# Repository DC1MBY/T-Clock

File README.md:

# T-Clock: A Nixie tube clock build from transistors only

The first working transistor demo just had its 75th anniversary: https://en.wikipedia.org/wiki/History_of_the_transistor How to better celebrate it than having (103 times) fun with transistors? Some time back I discovered in the German magazine Funkschau 1969 #2, #3 and #10 the article "Digital-Uhr zum Selbstbau", a copy of it can be found here: http://www.nixieuhren.de/downloads/digitaluhrfunkschau.pdf 
It is a Nixie clock design completely based on transistors. I always wanted to build one of these. When I found out that Kicad supports auto routing (freeRouting/LayoutEditor), that became much more feasible. This repository contains the PCB designs as well as OpenScad designs for the case and the spacer for the Nixies.

**Warning: Nixie tubes require high voltages which can be lethal. Please be careful!**

## Changes compared to the original

### Prescaler

I'm living in US, so I had to modify the prescaler from 50Hz to 60Hz mains frequency. /60 can be very easy implemented as /10 followed by /6. This allowed to re-use the PCBs of the first and second digit, just the decoding/high voltage transistors aren't populated on these PCBs. Luckily the usual PCB prototype manufactures always send a couple of copies of each ordered PCB, very handy for that.

### Schmitt-Trigger

The Schmitt trigger for converting the sinusoidal mains signal to a square wave feeding the prescaler was converted from Ge to Si. Because the circuit is small, I didn't develop a pcb for it but implemented it on a piece of perfboard. 

### Power Supply

Power source is a 12VAC 1.5A wall wart, this way no routing of mains voltage is needed. The high voltage for the Nixie tubes is generated by a small reverse operated transformer. Because of the high DC resistance of the transformer the supply is very soft and reaching the correct voltage (about 170V) is a bit critical. Therefore the rectified 12V was added in order to reach the required voltage. If this is needed or not will depend on the type of transformer. The Ge transistors of the 12V regulator were replaced by Si ones. The pass transistor needs a heatsink. A perfboard was used for the power supply. 

## Obtaining the parts

All components are easily obtainable except for the Nixie tubes. The IN-12 Nixie tube can still be found on ebay. Because the decimal point isn't used, both the IN-12A and IN-12B version will work fine.

## Block Diagram

## Mechanical

### Boards

The boards are stacked with 25mm M3 spacers and 10mm M3 spacers. The stack will be mounted to the case.

### Nixie

Even more difficult to source than the Nixie tubes themselves are sockets for them. Therefore I soldered the Nixie tubes directly to the PCB. I've seen this method first in Russian test equipment offered on a flea market. For equally spacing the Nixie from the PCB a 3d printed spacer is used (in12b.scad).  

### Case

The case is based on the fantastic Ultimate Box Maker https://github.com/jbebel/Ultimate-Box-Maker. The pcb mounts and the tabs are using M2.5 metal threaded inserts https://www.amazon.com/gp/product/B07NBPGTY2 .

The letters in the back panel are painted black with a sharpie. 

The screws can be installed with an Allen key through the vent. For the picture I didn't have the front panel installed yet, but the front panel needs to be installed before the screws. In this version of the case the tab was 2 mm thick and I broke one off. Therefore I made it 4mm thick. It might be best to print it with 100% infill for added stability.

## Summary

Things I might change if I'd redesign it:
- Move the Nixies to the center of the pcb for better looks
- Add a second mounting hole to the pcbs on the lower side (I made the usual mistake to first layout the pcbs and then think about the case)
- Change to SMD components. I forgot how tedious it is to bend the leads and clip them.   

That was a fun project. It turned out to be quite easy to build a more than 50 years old design today. I fear one of today's "modern" Nixie clock designs based on an microcontroller will be much harder to build in 50 years from now, the toolchain for the controller will not work with Windows 2070, USB20 will be incompatible with USB2.0, ... ;)

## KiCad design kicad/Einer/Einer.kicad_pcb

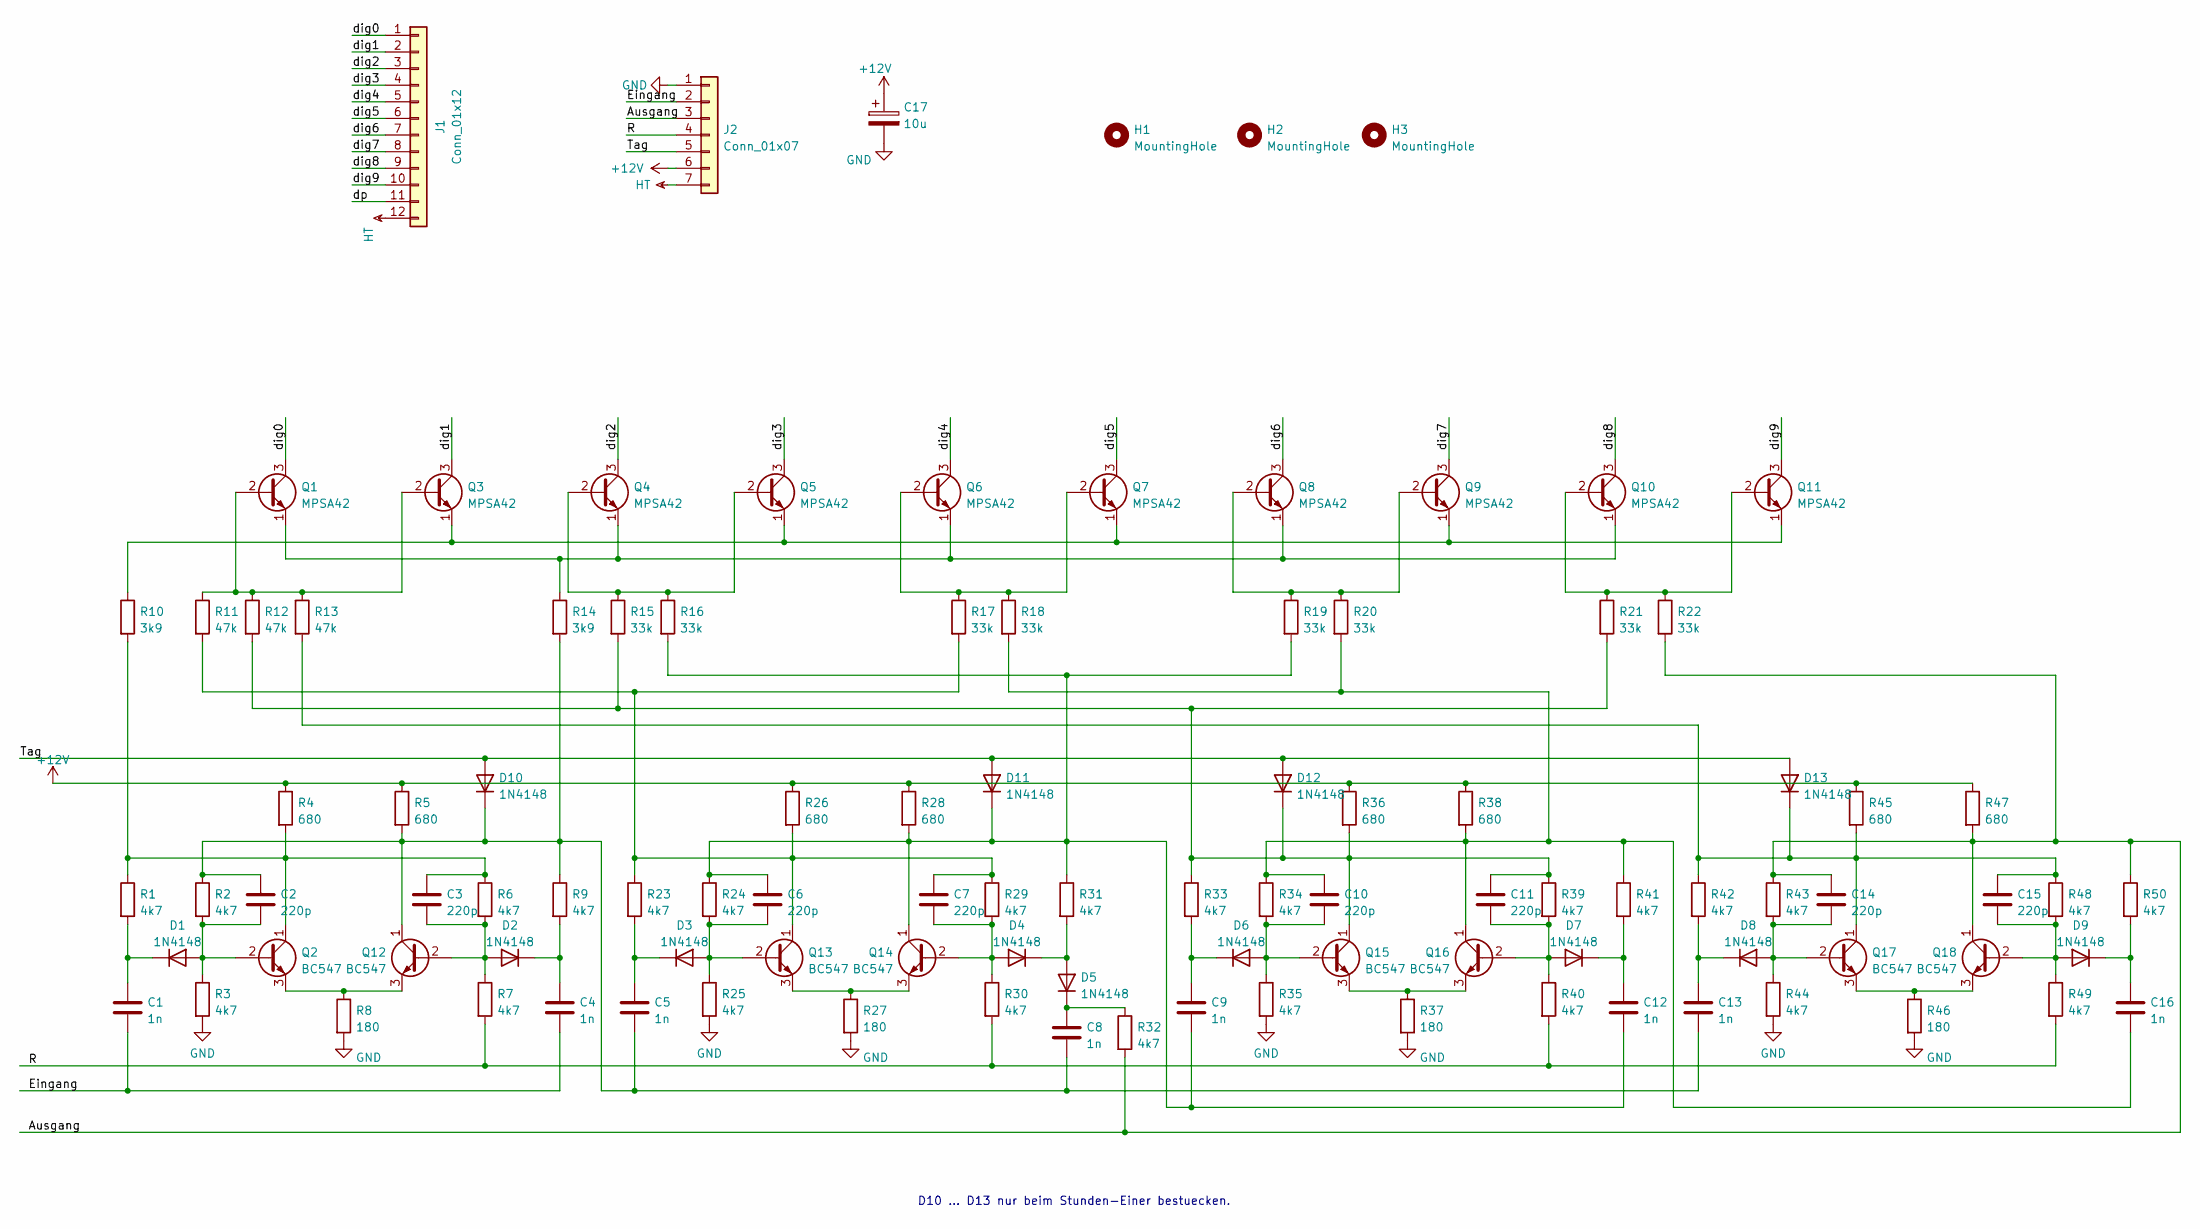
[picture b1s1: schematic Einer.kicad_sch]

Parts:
C1, C4, C5, C8, C9, C12, C13, C16: 1n; C_Disc_D5.0mm_W2.5mm_P2.50mm
C2, C3, C6, C7, C10, C11, C14, C15: 220p; C_Disc_D5.0mm_W2.5mm_P2.50mm
C17: 10u; CP_Radial_D5.0mm_P2.50mm
D1, D2, D3, D4, D5, D6, D7, D8, D9, D10, D11, D12, D13: 1N4148; D_DO-35_SOD27_P7.62mm_Horizontal
H1, H2, H3: MountingHole; MountingHole_3.2mm_M3
J1: Conn_01x12; PinHeader_1x12_P2.54mm_Vertical
J2: Conn_01x07; TerminalBlock_Phoenix_MKDS-3-7-5.08_1x07_P5.08mm_Horizontal
Q1, Q3, Q4, Q5, Q6, Q7, Q8, Q9, Q10, Q11: MPSA42; TO-92_HandSolder
Q2, Q12, Q13, Q14, Q15, Q16, Q17, Q18: BC547; TO-92_HandSolder
R1, R2, R3, R6, R7, R9, R23, R24, R25, R29, R30, R31, R32, R33, R34, R35, R39, R40, R41, R42, R43, R44, R48, R49, R50: 4k7; R_Axial_DIN0207_L6.3mm_D2.5mm_P10.16mm_Horizontal
R4, R5, R26, R28, R36, R38, R45, R47: 680; R_Axial_DIN0207_L6.3mm_D2.5mm_P10.16mm_Horizontal
R8, R27, R37, R46: 180; R_Axial_DIN0207_L6.3mm_D2.5mm_P10.16mm_Horizontal
R10, R14: 3k9; R_Axial_DIN0207_L6.3mm_D2.5mm_P10.16mm_Horizontal
R11, R12, R13: 47k; R_Axial_DIN0207_L6.3mm_D2.5mm_P10.16mm_Horizontal
R15, R16, R17, R18, R19, R20, R21, R22: 33k; R_Axial_DIN0207_L6.3mm_D2.5mm_P10.16mm_Horizontal

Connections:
+12V: C17.1, J2.6, R4.1, R5.1, R26.1, R28.1, R36.1, R38.1, R45.1, R47.1
/Ausgang: C14.1, J2.3, Q18.1 (C), R22.2, R32.2, R43.1, R47.2, R50.1
/Eingang: C1.2, C4.2, J2.2
/R: J2.4, R7.2, R30.2, R40.2, R49.2
/Tag: D10.2 (A), D11.2 (A), D12.2 (A), D13.2 (A), J2.5
/dig0: J1.1, Q1.3 (C)
/dig1: J1.2, Q3.3 (C)
/dig2: J1.3, Q4.3 (C)
/dig3: J1.4, Q5.3 (C)
/dig4: J1.5, Q6.3 (C)
/dig5: J1.6, Q7.3 (C)
/dig6: J1.7, Q8.3 (C)
/dig7: J1.8, Q9.3 (C)
/dig8: J1.9, Q10.3 (C)
/dig9: J1.10, Q11.3 (C)
/dp: J1.11
GND: C17.2, J2.1, R3.2, R8.2, R25.2, R27.2, R35.2, R37.2, R44.2, R46.2
HT: J1.12, J2.7
unnamed: C1.1, D1.1 (K), R1.2
unnamed: C2.2, D1.2 (A), Q2.2 (B), R2.2, R3.1
unnamed: C3.1, Q2.1 (C), R1.1, R4.2, R6.1, R10.2
unnamed: C3.2, D2.2 (A), Q12.2 (B), R6.2, R7.1
unnamed: C4.1, D2.1 (K), R9.2
unnamed: C5.1, D3.1 (K), R23.2
unnamed: C6.2, D3.2 (A), Q13.2 (B), R24.2, R25.1
unnamed: C7.1, Q13.1 (C), R11.2, R17.2, R23.1, R26.2, R29.1
unnamed: C7.2, D4.2 (A), Q14.2 (B), R29.2, R30.1
unnamed: C8.1, D5.1 (K), R32.1
unnamed: C9.1, D6.1 (K), R33.2
unnamed: C10.1, C16.2, Q16.1 (C), R18.2, R20.2, R34.1, R38.2, R41.1
unnamed: C10.2, D6.2 (A), Q15.2 (B), R34.2, R35.1
unnamed: C11.1, D12.1 (K), Q15.1 (C), R12.2, R15.2, R21.2, R33.1, R36.2, R39.1
unnamed: C11.2, D7.2 (A), Q16.2 (B), R39.2, R40.1
unnamed: C12.1, D7.1 (K), R41.2
unnamed: C6.1, C9.2, C12.2, D11.1 (K), Q14.1 (C), R16.2, R19.2, R24.1, R28.2, R31.1
unnamed: C13.1, D8.1 (K), R42.2
unnamed: C2.1, C5.2, C8.2, C13.2, D10.1 (K), Q12.1 (C), R2.1, R5.2, R9.1, R14.2
unnamed: C14.2, D8.2 (A), Q17.2 (B), R43.2, R44.1
unnamed: C15.1, D13.1 (K), Q17.1 (C), R13.2, R42.1, R45.2, R48.1
unnamed: C15.2, D9.2 (A), Q18.2 (B), R48.2, R49.1
unnamed: C16.1, D9.1 (K), R50.2
unnamed: D4.1 (K), D5.2 (A), R31.2
unnamed: Q1.1 (E), Q4.1 (E), Q6.1 (E), Q8.1 (E), Q10.1 (E), R14.1
unnamed: Q1.2 (B), Q3.2 (B), R11.1, R12.1, R13.1
unnamed: Q4.2 (B), Q5.2 (B), R15.1, R16.1
unnamed: Q6.2 (B), Q7.2 (B), R17.1, R18.1
unnamed: Q8.2 (B), Q9.2 (B), R19.1, R20.1
unnamed: Q10.2 (B), Q11.2 (B), R21.1, R22.1
unnamed: Q3.1 (E), Q5.1 (E), Q7.1 (E), Q9.1 (E), Q11.1 (E), R10.1
unnamed: Q2.3 (E), Q12.3 (E), R8.1
unnamed: Q13.3 (E), Q14.3 (E), R27.1
unnamed: Q15.3 (E), Q16.3 (E), R37.1
unnamed: Q17.3 (E), Q18.3 (E), R46.1

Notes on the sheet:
D10 ... D13 nur beim Stunden-Einer bestuecken.

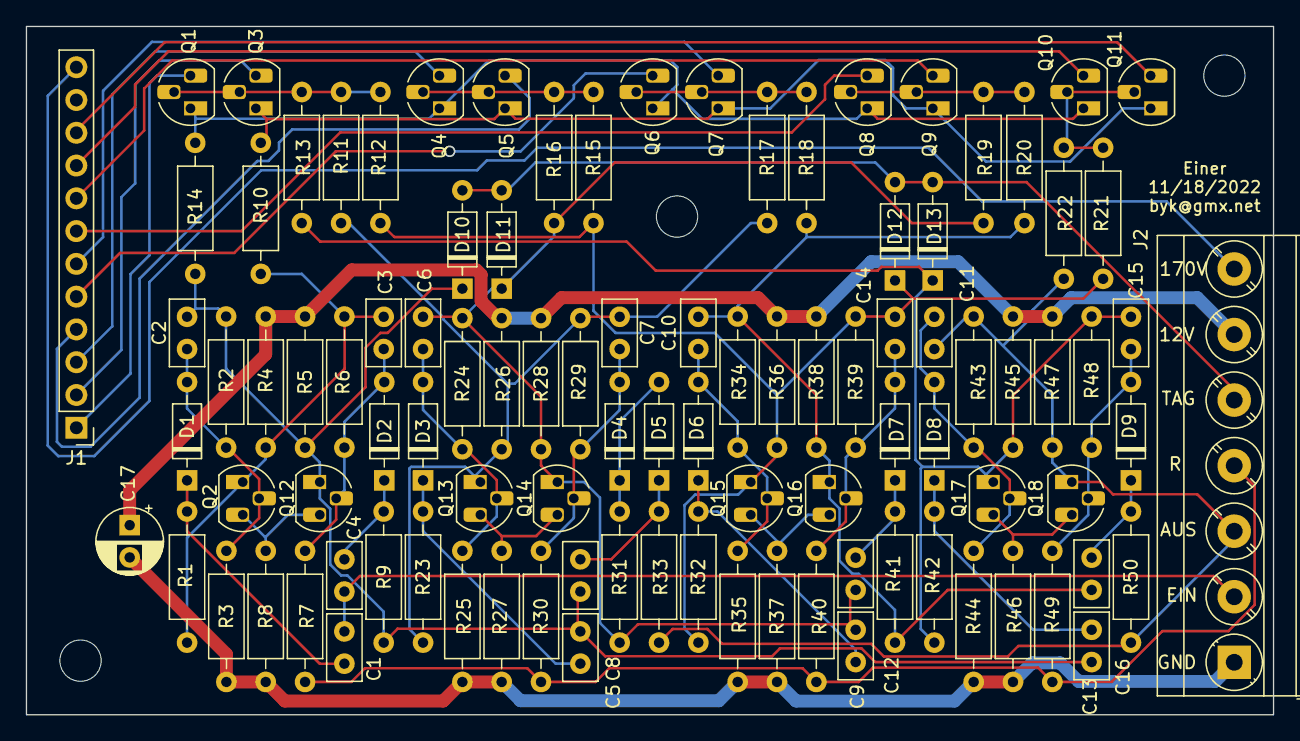
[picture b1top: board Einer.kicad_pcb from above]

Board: 2 copper layers, 96.6 x 53.3 mm, 103 parts (0 on the bottom side), 52 nets.

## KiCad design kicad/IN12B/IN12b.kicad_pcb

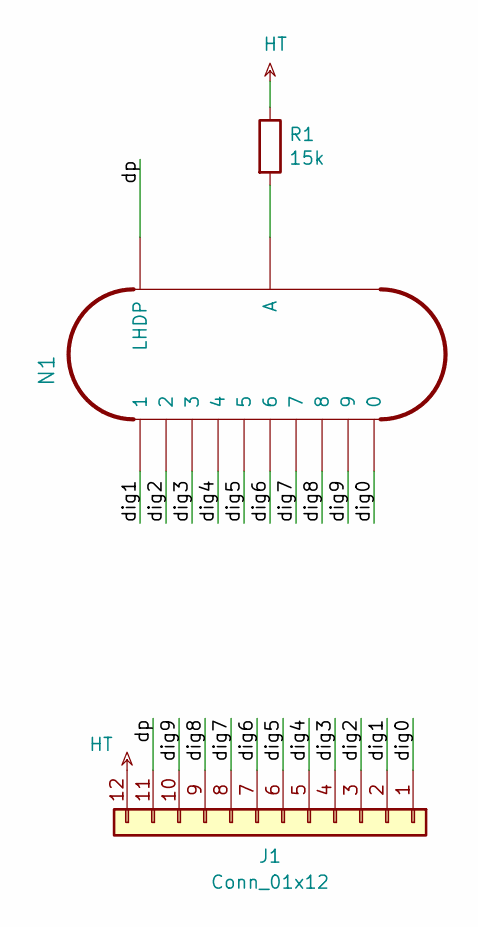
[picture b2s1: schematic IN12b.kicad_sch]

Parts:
J1: Conn_01x12; PinHeader_1x12_P2.54mm_Horizontal
N1: IN-12B; IN-12
R1: 15k; R_Axial_DIN0207_L6.3mm_D2.5mm_P10.16mm_Horizontal

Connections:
/dig0: J1.1, N1.0
/dig1: J1.2, N1.1
/dig2: J1.3, N1.2
/dig3: J1.4, N1.3
/dig4: J1.5, N1.4
/dig5: J1.6, N1.5
/dig6: J1.7, N1.6
/dig7: J1.8, N1.7
/dig8: J1.9, N1.8
/dig9: J1.10, N1.9
/dp: J1.11, N1.LHDP
HT: J1.12, R1.1
unnamed: N1.A, R1.2

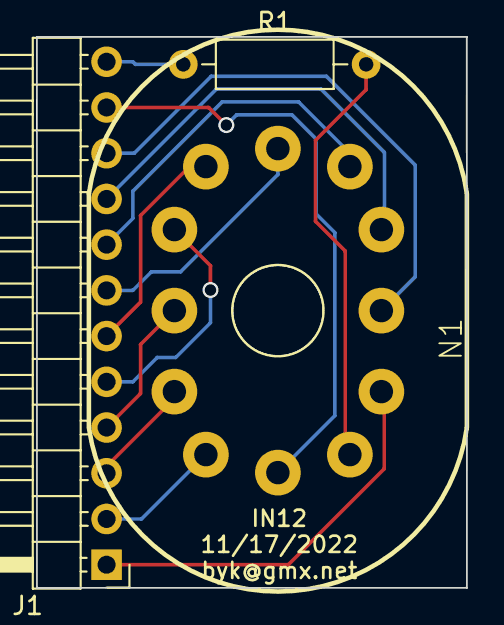
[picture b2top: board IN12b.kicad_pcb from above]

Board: 2 copper layers, 23.9 x 30.6 mm, 3 parts (0 on the bottom side), 13 nets.

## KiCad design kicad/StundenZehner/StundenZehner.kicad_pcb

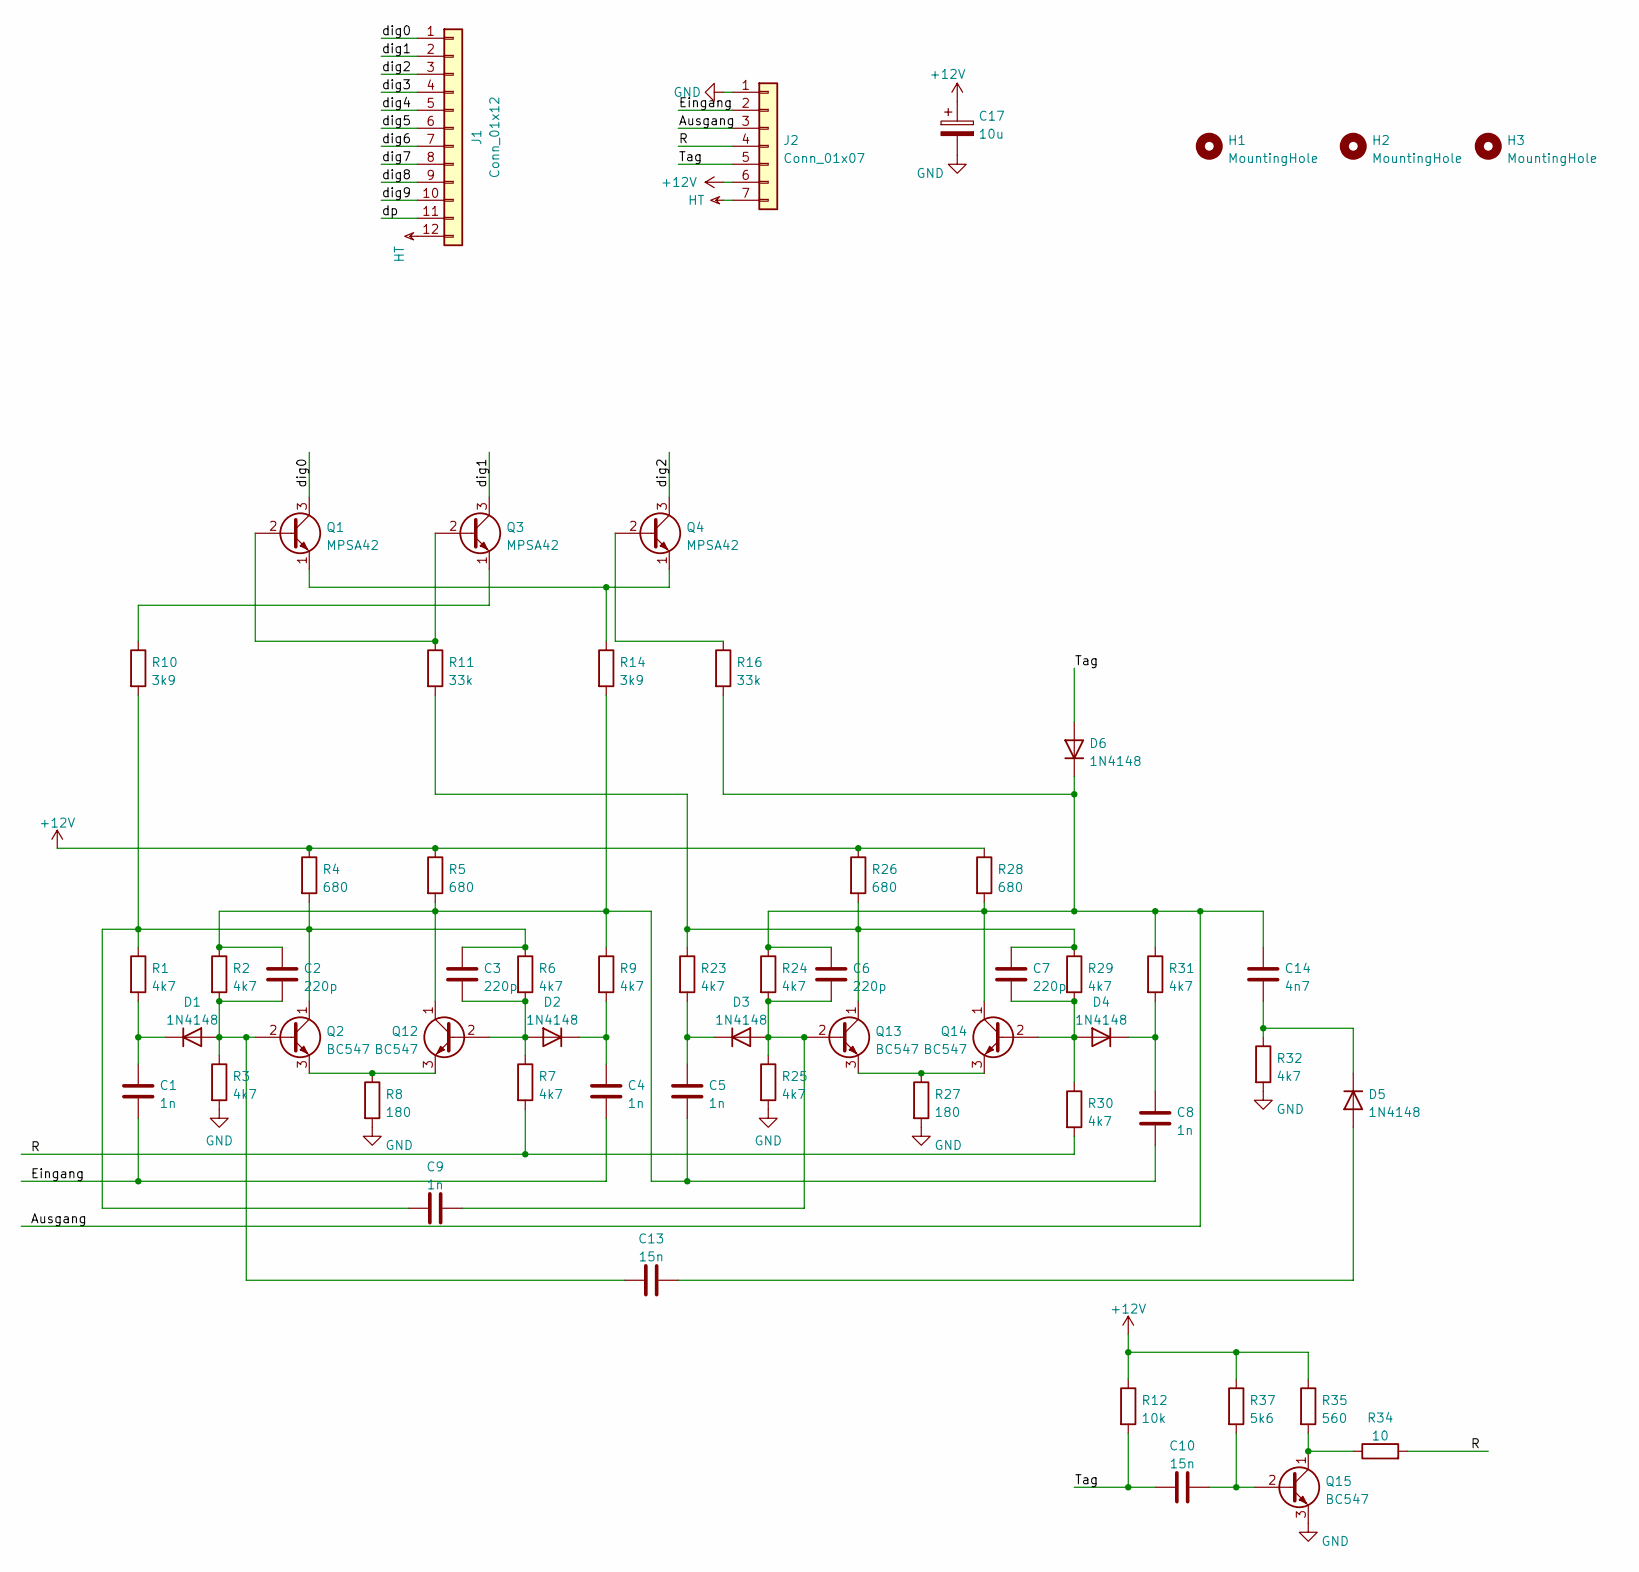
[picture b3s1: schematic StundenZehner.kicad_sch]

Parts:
C1, C4, C5, C8, C9: 1n; C_Disc_D5.0mm_W2.5mm_P2.50mm
C2, C3, C6, C7: 220p; C_Disc_D5.0mm_W2.5mm_P2.50mm
C10, C13: 15n; C_Disc_D5.0mm_W2.5mm_P2.50mm
C14: 4n7; C_Disc_D5.0mm_W2.5mm_P2.50mm
C17: 10u; CP_Radial_D5.0mm_P2.50mm
D1, D2, D3, D4, D5, D6: 1N4148; D_DO-35_SOD27_P7.62mm_Horizontal
H1, H2, H3: MountingHole; MountingHole_3.2mm_M3
J1: Conn_01x12; PinHeader_1x12_P2.54mm_Vertical
J2: Conn_01x07; TerminalBlock_Phoenix_MKDS-3-7-5.08_1x07_P5.08mm_Horizontal
Q1, Q3, Q4: MPSA42; TO-92_HandSolder
Q2, Q12, Q13, Q14, Q15: BC547; TO-92_HandSolder
R1, R2, R3, R6, R7, R9, R23, R24, R25, R29, R30, R31, R32: 4k7; R_Axial_DIN0207_L6.3mm_D2.5mm_P10.16mm_Horizontal
R4, R5, R26, R28: 680; R_Axial_DIN0207_L6.3mm_D2.5mm_P10.16mm_Horizontal
R8, R27: 180; R_Axial_DIN0207_L6.3mm_D2.5mm_P10.16mm_Horizontal
R10, R14: 3k9; R_Axial_DIN0207_L6.3mm_D2.5mm_P10.16mm_Horizontal
R11, R16: 33k; R_Axial_DIN0207_L6.3mm_D2.5mm_P10.16mm_Horizontal
R12: 10k; R_Axial_DIN0207_L6.3mm_D2.5mm_P10.16mm_Horizontal
R34: 10; R_Axial_DIN0207_L6.3mm_D2.5mm_P10.16mm_Horizontal
R35: 560; R_Axial_DIN0207_L6.3mm_D2.5mm_P10.16mm_Horizontal
R37: 5k6; R_Axial_DIN0207_L6.3mm_D2.5mm_P10.16mm_Horizontal

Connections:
+12V: C17.1, J2.6, R4.1, R5.1, R12.1, R26.1, R28.1, R35.1, R37.1
/Ausgang: C6.1, C14.1, D6.1 (K), J2.3, Q14.1 (C), R16.2, R24.1, R28.2, R31.1
/Eingang: C1.2, C4.2, J2.2
/R: J2.4, R7.2, R30.2, R34.2
/Tag: C10.1, D6.2 (A), J2.5, R12.2
/dig0: J1.1, Q1.3 (C)
/dig1: J1.2, Q3.3 (C)
/dig2: J1.3, Q4.3 (C)
/dig3: J1.4
/dig4: J1.5
/dig5: J1.6
/dig6: J1.7
/dig7: J1.8
/dig8: J1.9
/dig9: J1.10
/dp: J1.11
GND: C17.2, J2.1, Q15.3 (E), R3.2, R8.2, R25.2, R27.2, R32.2
HT: J1.12, J2.7
unnamed: C1.1, D1.1 (K), R1.2
unnamed: C2.1, C5.2, C8.2, Q12.1 (C), R2.1, R5.2, R9.1, R14.2
unnamed: C3.1, C9.1, Q2.1 (C), R1.1, R4.2, R6.1, R10.2
unnamed: C3.2, D2.2 (A), Q12.2 (B), R6.2, R7.1
unnamed: C4.1, D2.1 (K), R9.2
unnamed: C5.1, D3.1 (K), R23.2
unnamed: C6.2, C9.2, D3.2 (A), Q13.2 (B), R24.2, R25.1
unnamed: C7.1, Q13.1 (C), R11.2, R23.1, R26.2, R29.1
unnamed: C7.2, D4.2 (A), Q14.2 (B), R29.2, R30.1
unnamed: C8.1, D4.1 (K), R31.2
unnamed: C10.2, Q15.2 (B), R37.2
unnamed: C2.2, C13.1, D1.2 (A), Q2.2 (B), R2.2, R3.1
unnamed: C13.2, D5.2 (A)
unnamed: C14.2, D5.1 (K), R32.1
unnamed: Q1.1 (E), Q4.1 (E), R14.1
unnamed: Q1.2 (B), Q3.2 (B), R11.1
unnamed: Q3.1 (E), R10.1
unnamed: Q4.2 (B), R16.1
unnamed: Q2.3 (E), Q12.3 (E), R8.1
unnamed: Q13.3 (E), Q14.3 (E), R27.1
unnamed: Q15.1 (C), R34.1, R35.2

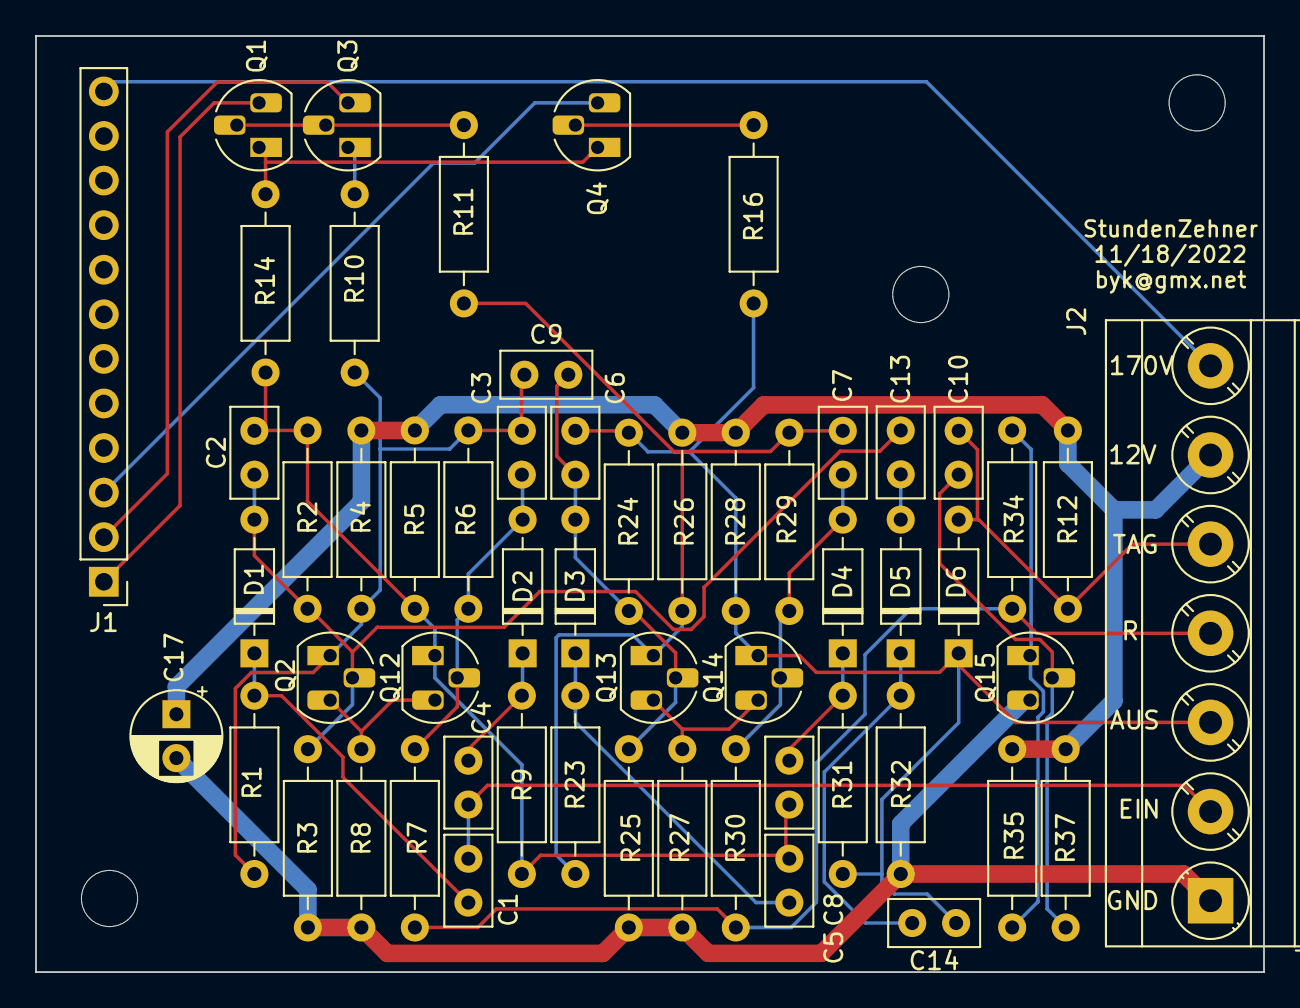
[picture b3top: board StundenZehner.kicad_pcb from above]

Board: 2 copper layers, 70.0 x 53.3 mm, 59 parts (0 on the bottom side), 31 nets.

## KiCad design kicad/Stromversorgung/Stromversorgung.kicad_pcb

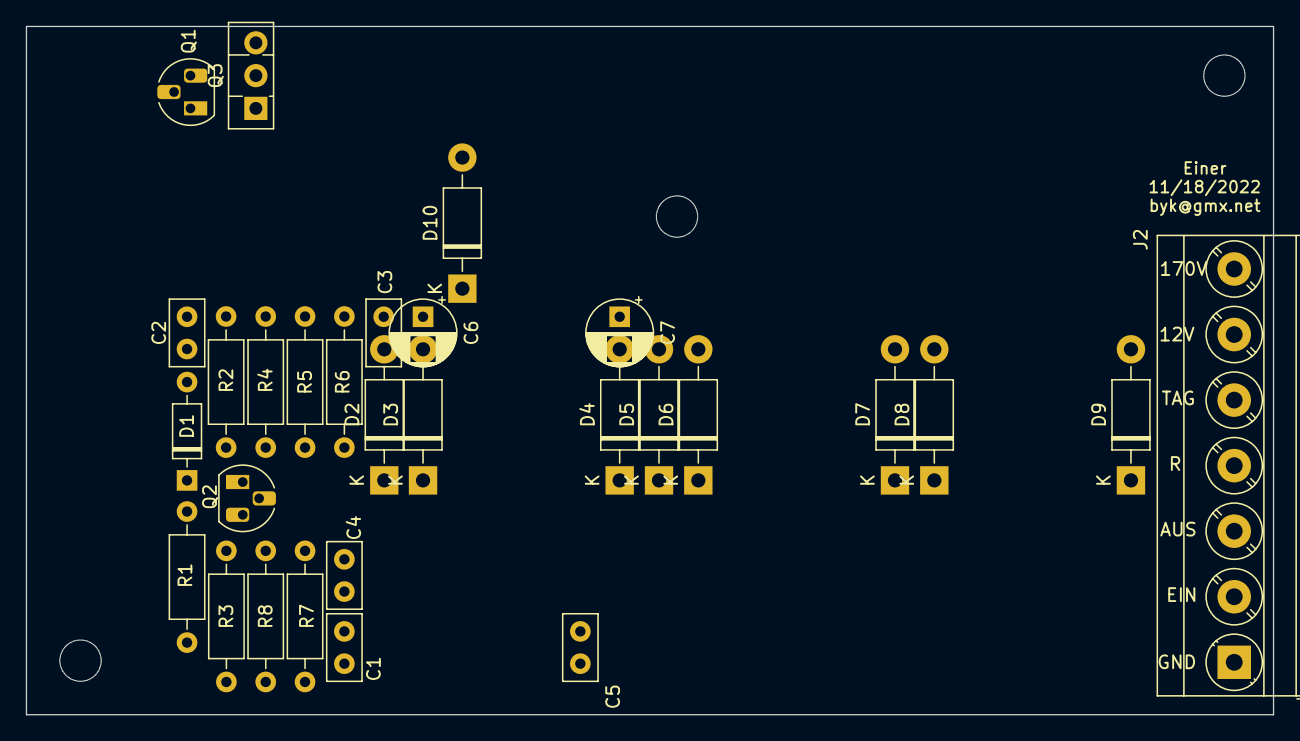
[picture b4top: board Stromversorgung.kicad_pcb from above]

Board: 2 copper layers, 96.6 x 53.3 mm, 32 parts (0 on the bottom side), 15 nets, no tracks yet.

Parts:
C1: 100n; C_Disc_D5.0mm_W2.5mm_P2.50mm
C2: 220p; C_Disc_D5.0mm_W2.5mm_P2.50mm
C3, C4, C5: 1n; C_Disc_D5.0mm_W2.5mm_P2.50mm
C6, C7: 10u; CP_Radial_D5.0mm_P2.50mm
D1: 1N4148; D_DO-35_SOD27_P7.62mm_Horizontal
D2, D3, D4, D5, D6, D7, D8, D9: 1N4004; D_DO-41_SOD81_P10.16mm_Horizontal
D10: 12V; D_DO-41_SOD81_P10.16mm_Horizontal
H1, H2, H3: MountingHole; MountingHole_3.2mm_M3
J2: Conn_01x07; TerminalBlock_Phoenix_MKDS-3-7-5.08_1x07_P5.08mm_Horizontal
Q1, Q2: BC547; TO-92_HandSolder
Q3: BD135; TO-126-3_Vertical
R1, R4: 22k; R_Axial_DIN0207_L6.3mm_D2.5mm_P10.16mm_Horizontal
R2, R3: 2k2; R_Axial_DIN0207_L6.3mm_D2.5mm_P10.16mm_Horizontal
R5: 330; R_Axial_DIN0207_L6.3mm_D2.5mm_P10.16mm_Horizontal
R6: 10k; R_Axial_DIN0207_L6.3mm_D2.5mm_P10.16mm_Horizontal
R7: 680; R_Axial_DIN0207_L6.3mm_D2.5mm_P10.16mm_Horizontal
R8: 2M2; R_Axial_DIN0207_L6.3mm_D2.5mm_P10.16mm_Horizontal

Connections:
12VAC1: D2.2 (A), D4.1 (K), J2.2, R1.1
12VAC2: D3.2 (A), D5.1 (K), J2.3
+12V: C7.1, J2.6, Q3.1 (E), R2.1, R3.1
GND: C1.2, C6.2, C7.2, D1.2 (A), D4.2 (A), D5.2 (A), D8.2 (A), D9.2 (A), D10.2 (A), J2.1, R5.2, R6.2, R8.2
HT: D6.1 (K), D7.1 (K), J2.7, R8.1
unnamed: C1.1, D1.1 (K), Q1.2 (B), R1.2
unnamed: D2.1 (K), D3.1 (K), Q3.2 (C), R7.1
unnamed: C3.1, Q1.1 (C), R2.2, R4.1
unnamed: C3.2, Q2.2 (B), R4.2, R6.1
unnamed: C6.1, D10.1 (K), Q3.3 (B), R7.2
unnamed: C2.1, C5.2
unnamed: D6.2 (A), D8.1 (K)
unnamed: D7.2 (A), D9.1 (K)
unnamed: Q1.3 (E), Q2.3 (E), R5.1
Takt: J2.4, Q2.1 (C), R3.2

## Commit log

2022-12-17 Initial commit.
2022-12-17 Added Kicad and Openscad files
2022-12-31 Added more pictures
2022-12-31 Updated Readme, added box Openscad file
2022-12-31 Resized Nixie image
2022-12-31 Added block diagram
